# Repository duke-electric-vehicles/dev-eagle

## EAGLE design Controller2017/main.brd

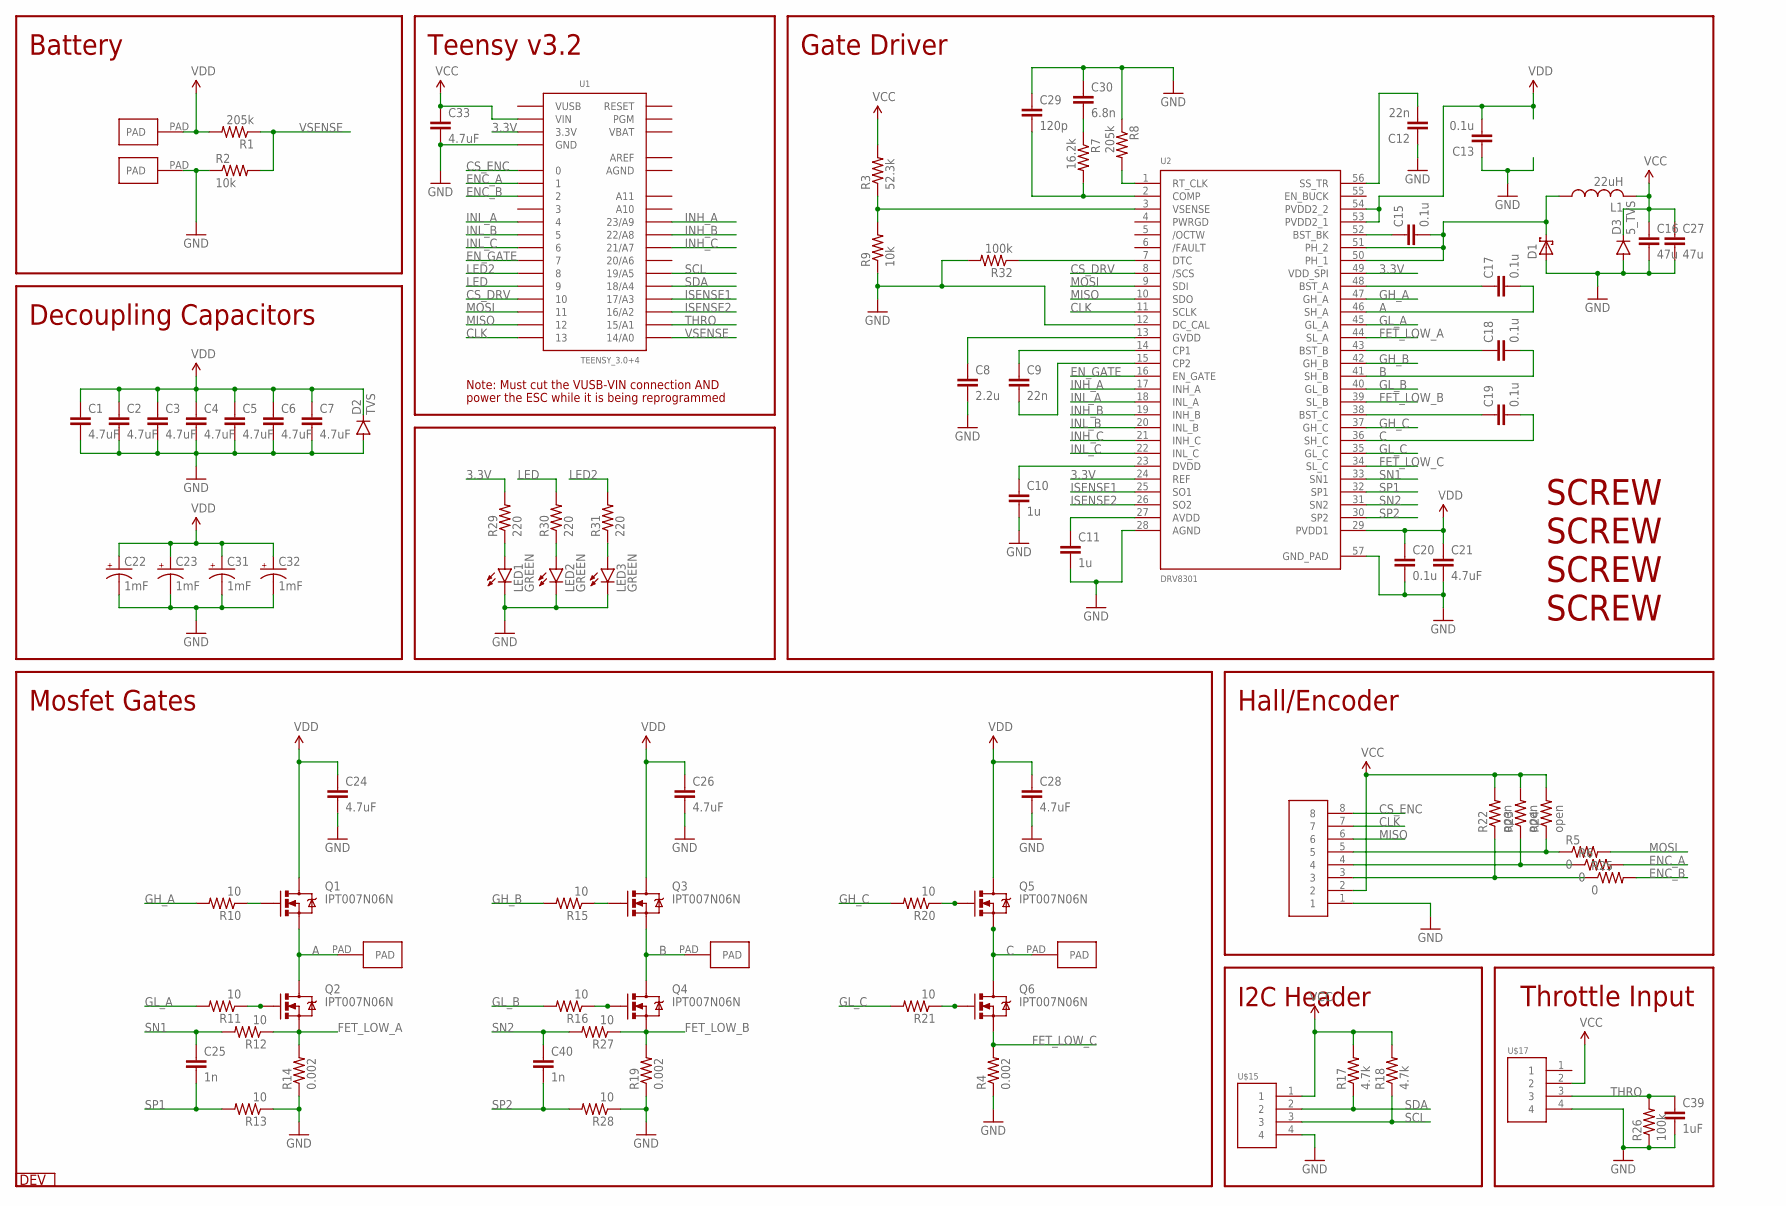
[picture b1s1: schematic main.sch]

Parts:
C1, C2, C3, C4, C5, C6, C7, C21, C24, C26, C28, C33: 4.7uF; 1206
C8: 2.2u; 0603-CAP
C9, C12: 22n; 0603-CAP
C10, C11: 1u; 0603-CAP
C13, C15, C17, C18, C19, C20: 0.1u; 0603-CAP
C16, C27: 47u; 0805
C22, C23, C31, C32: 1mF; CPOL-RADIAL-1000UF-25V
C25, C40: 1n; 0603-CAP
C29: 120p; 0603-CAP
C30: 6.8n; 0603-CAP
C39: 1uF; 0603-CAP
D1: SCHOTTKY_SMA; SMA
D2: TVS; SMC
D3: 5_TVS; SOT23-3
L1: 22uH; L5650M
LED1, LED2, LED3: GREEN; LED-1206
Q1, Q2, Q3, Q4, Q5, Q6: IPT007N06N; PG-HSOF-8-1
R1, R8: 205k; 0603-RES
R2, R9: 10k; 0603-RES
R3: 52.3k; 0603-RES
R4, R14, R19: 0.002; R2512
R5, R6, R25: 0; 0603-RES
R7: 16.2k; 0603-RES
R10, R11, R12, R13, R15, R16, R20, R21, R27, R28: 10; 0603-RES
R17, R18: 4.7k; 0603-RES
R22, R23, R24: open; 0603-RES
R26, R32: 100k; 0603-RES
R29, R30, R31: 220; 0603-RES
U1: TEENSY_3.0+4
U2: DRV8301
U$2: HEADER8; 8PINVALULOK
U$15, U$17: HEADER4VALULOK; 4PINVALULOK
U$16: DEV
U$19, U$20, U$21, U$22: SCREW; M3HOLE
U$23, U$24, U$25, U$26, U$27: PAD

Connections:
3.3V: R29.2, U1.3.3V, U1.3.3V1 (3.3V), U2.24 (REF), U2.49 (VDD_SPI)
A: C17.2, Q1.S, Q2.D, U2.46 (SH_A), U$23.PAD
AGND: U1.AGND
AREF: U1.AREF
B: C18.2, Q3.S, Q4.D, U2.41 (SH_B), U$24.PAD
C: C19.2, Q5.S, Q6.D, U2.36 (SH_C), U$25.PAD
CLK: U1.13, U2.11 (SCLK), U$2.7
CS_DRV: U1.10, U2.8 (/SCS)
CS_ENC: U1.0, U$2.8
ENC_A: R6.2, U1.1
ENC_B: R25.2, U1.2
EN_GATE: U1.7, U2.16 (EN_GATE)
FET_LOW_A: Q2.S, R12.1, R14.2, U2.44 (SL_A)
FET_LOW_B: Q4.S, R19.2, R27.1, U2.39 (SL_B)
FET_LOW_C: Q6.S, R4.2, U2.34 (SL_C)
GH_A: R10.2, U2.47 (GH_A)
GH_B: R15.2, U2.42 (GH_B)
GH_C: R20.2, U2.37 (GH_C)
GL_A: R11.2, U2.45 (GL_A)
GL_A': Q2.G, R11.1
GL_B: R16.2, U2.40 (GL_B)
GL_B': Q4.G, R16.1
GL_C: R21.2, U2.35 (GL_C)
GL_C': Q6.G, R21.1
GND: C1.2, C2.2, C3.2, C4.2, C5.2, C6.2, C7.2, C8.2, C10.2, C11.2, C12.1, C13.1, C16.2, C20.2, C21.2, C22.-, C23.-, C24.2, C26.2, C27.2, C28.2, C29.1, C30.1, C31.-, C32.-, C33.2, C39.2, D1.A, D2.A, D3.1 (A), LED1.C, LED2.C, LED3.C, R2.1, R4.1, R8.1, R9.1, R13.1, R14.1, R19.1, R26.1, R28.1, R32.2, U1.GND, U1.GND1 (GND), U2.12 (DC_CAL), U2.28 (AGND), U2.57 (GND_PAD), U$2.1, U$15.4, U$17.4, U$27.PAD
INH_A: U1.23/A9, U2.17 (INH_A)
INH_B: U1.22/A8, U2.19 (INH_B)
INH_C: U1.21/A7, U2.21 (INH_C)
INL_A: U1.4, U2.18 (INL_A)
INL_B: U1.5, U2.20 (INL_B)
INL_C: U1.6, U2.22 (INL_C)
ISENSE1: U1.17/A3, U2.25 (SO1)
ISENSE2: U1.16/A2, U2.26 (SO2)
LED: R30.2, U1.9
LED2: R31.2, U1.8
MISO: U1.12, U2.10 (SDO), U$2.6
MOSI: R5.2, U1.11, U2.9 (SDI)
unnamed: Q3.G, R15.1
unnamed: R3.1, R9.2, U2.3 (VSENSE)
unnamed: C29.2, R7.2, U2.2 (COMP)
unnamed: C10.1, U2.23 (DVDD)
unnamed: Q5.G, R20.1
unnamed: C12.2, U2.56 (SS_TR)
unnamed: C30.2, R7.1
unnamed: C15.1, U2.52 (BST_BK)
unnamed: Q1.G, R10.1
unnamed: R8.2, U2.1 (RT_CLK)
unnamed: LED1.A, R29.1
unnamed: R32.1, U2.7 (DTC)
unnamed: R5.1, R24.1, U$2.5
unnamed: R6.1, R23.1, U$2.4
unnamed: R22.1, R25.1, U$2.3
unnamed: LED2.A, R30.1
unnamed: LED3.A, R31.1
unnamed: C19.1, U2.38 (BST_C)
unnamed: C9.1, U2.14 (CP1)
unnamed: C11.1, U2.27 (AVDD)
unnamed: C9.2, U2.15 (CP2)
unnamed: C8.1, U2.13 (GVDD)
unnamed: C18.1, U2.43 (BST_B)
unnamed: C17.1, U2.48 (BST_A)
unnamed: C15.2, D1.C, L1.1, U2.50 (PH_1), U2.51 (PH_2)
SCL: R18.1, U1.19/A5, U$15.3
SDA: R17.1, U1.18/A4, U$15.2
SN1: C25.1, R12.2, U2.33 (SN1)
SN2: C40.1, R27.2, U2.31 (SN2)
SP1: C25.2, R13.2, U2.32 (SP1)
SP2: C40.2, R28.2, U2.30 (SP2)
THRO: C39.1, R26.2, U1.15/A1, U$17.3
VBAT: U1.VBAT
VCC: C16.1, C27.1, C33.1, D3.3 (C), L1.2, R3.2, R17.2, R18.2, R22.2, R23.2, R24.2, U1.VIN, U$2.2, U$15.1, U$17.2
VDD: C1.1, C2.1, C3.1, C4.1, C5.1, C6.1, C7.1, C13.2, C20.1, C21.1, C22.+, C23.+, C24.1, C26.1, C28.1, C31.+, C32.+, D2.C, Q1.D, Q3.D, Q5.D, R1.2, U2.29 (PVDD1), U2.53 (PVDD2_1), U2.54 (PVDD2_2), U$26.PAD
VSENSE: R1.1, R2.2, U1.14/A0
VUSB: U1.VUSB

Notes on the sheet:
Teensy v3.2
Gate Driver
Mosfet Gates
Battery
Hall/Encoder
Decoupling Capacitors
Note: Must cut the VUSB-VIN connection AND
power the ESC while it is being reprogrammed
Throttle Input
I2C Header

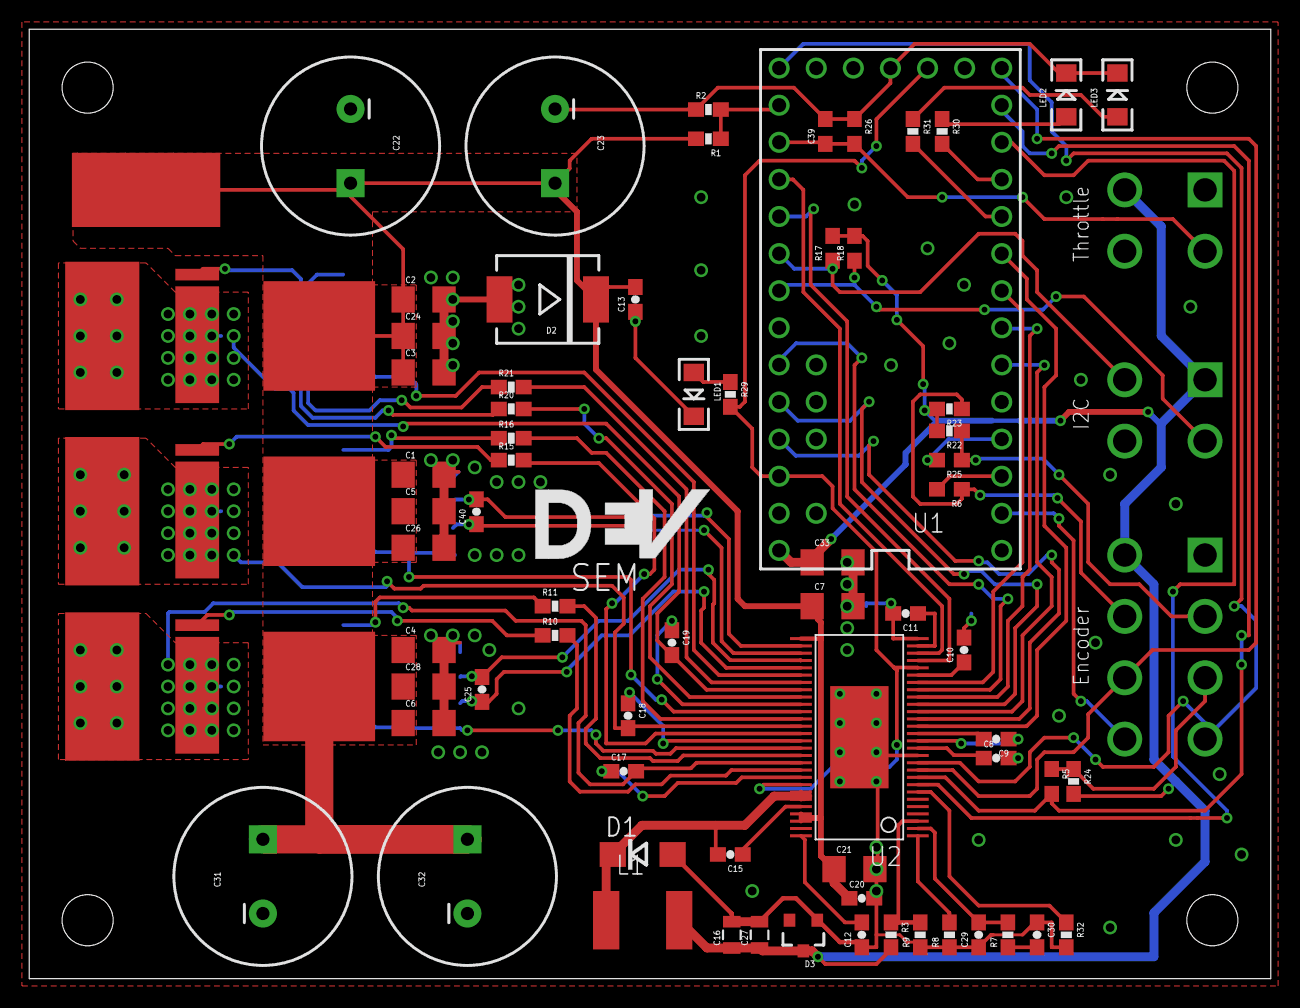
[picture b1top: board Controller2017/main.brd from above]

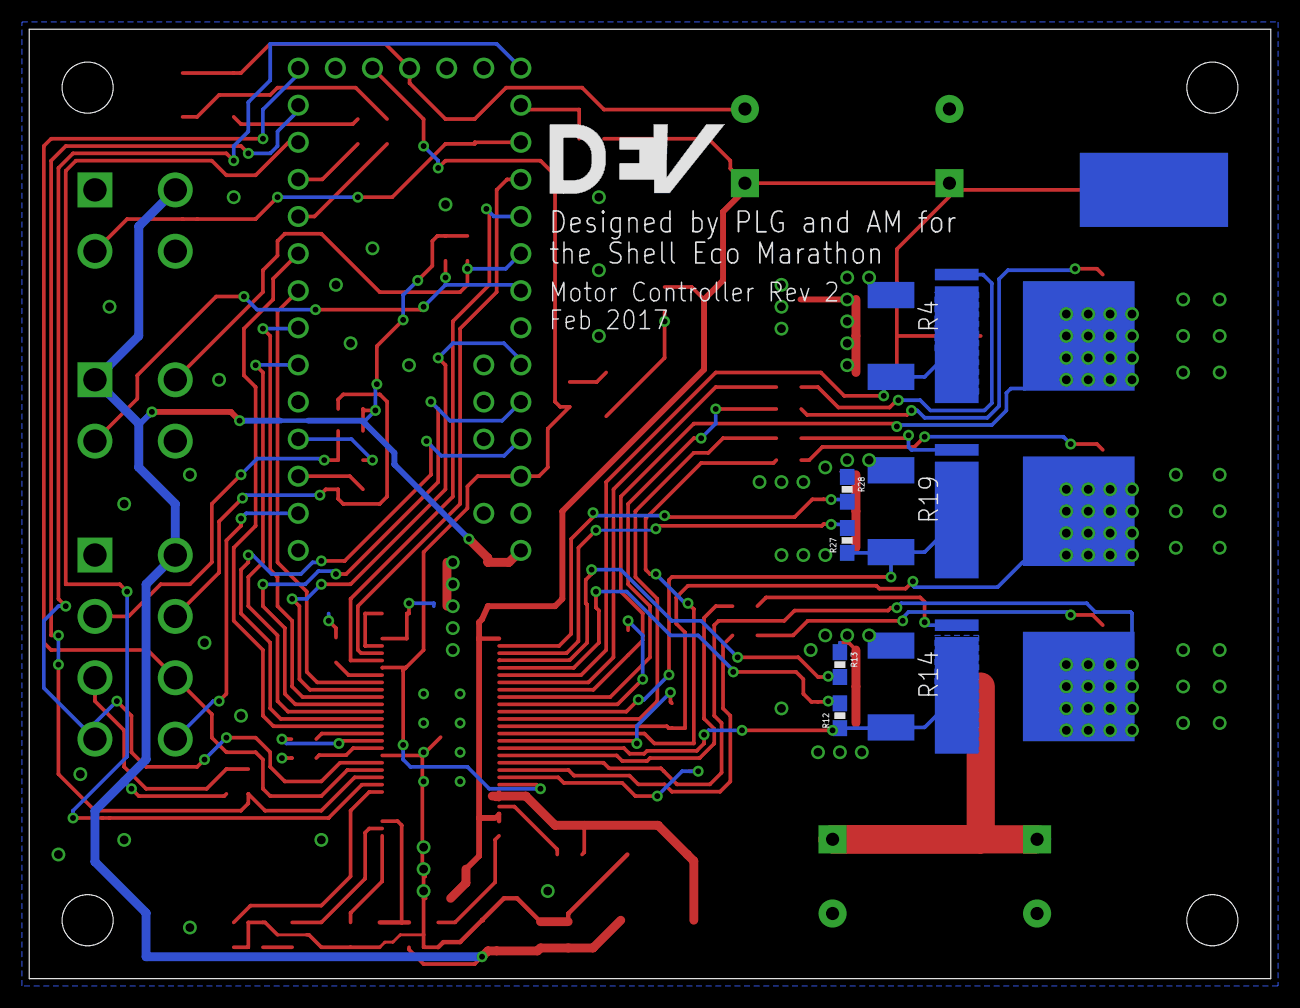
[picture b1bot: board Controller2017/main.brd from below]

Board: 2 copper layers, 85.0 x 65.0 mm, 95 parts (12 on the bottom side), 70 nets.

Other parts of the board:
U$28: DEV

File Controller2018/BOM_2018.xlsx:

Description | Digikey Part # | Value | Components | Price | Qty | Total |  | Grand total | 70.48
Teensy 3.2 | 1568-1231-ND |  | U1 | 22.5 | 1 | 22.5 | yes
DRV8301 | 296-29433-1-ND |  | U2 | 6.14 | 1 | 6.14 | yes
NFET | NVMFS5C404NLAFT1GOSCT-ND |  | Q1 Q2 Q3 Q4 Q5 Q6 | 3.47 | 6 | 20.82 | yes
TVS | 497-6522-1-ND | 48V | D2 | 0.53 | 1 | 0.53 | yes
TVS | GSOT05-E3-08CT-ND | 5v | D3 | 0.38 | 1 | 0.38 | yes
Quad Op-apm | 296-11968-1-ND |  |  | 2.0099999999999998 | 1 | 2.0099999999999998
PFET | 785-1001-1-ND |  |  | 0.48 | 1 | 0.48
 |  |  |  |  |  | 0
LED 1206 | 160-1456-1-ND | Green | LED1 LED2 LED3 | 0.34 | 3 | 1.02 | yes
Ceramic cap 50V 0603 | 490-1429-1-ND | 120pF | C29 | 0.01 | 1 | 0.01
Ceramic cap 50V 0603 | 399-1089-1-ND | 6.8nF | C30 | 0.01 | 1 | 0.01
Resistor 0603 | 311-16.2KHRCT-ND | 16.2k | R7 | 0.01 | 1 | 0.01
Resistor 0603 | 311-52.3KHRCT-ND | 52.3k | R3 | 0.01 | 1 | 0.01 | yes
Inductor | 587-2952-1-ND | 22uH | L1 | 0.43 | 1 | 0.43 | yes
Ceramic cap 6.3V 0805 | 311-1897-1-ND | 47uF | C16 C27 | 0.46 | 2 | 0.92
Schottkey diode | 641-1701-1-ND | 200V 3A | D1 | 0.43 | 1 | 0.43 | yes
Ceramic cap 16V 0603 | 490-3296-1-ND | 2.2uF | C8 | 0.1 | 1 | 0.1
Ceramic cap 50V 0603 | 490-1500-6-ND | 22nF | C9 C12 | 0.01 | 2 | 0.02 | yes
Ceramic cap 50V 0603 | 490-1519-6-ND | 0.1uF | C13 C15 C17 C18 C19 C20 C22 C23 | 0.01 | 8 | 0.08 | yes
Ceramic cap 25V 0805 | 490-3335-6-ND | 4.7uF | C14 C21 C35 | 0.1 | 3 | 0.30000000000000004
Ceramic cap 25V 0603 | 490-6339-6-ND | 10nF | C36 C37 C38 | 0.01 | 3 | 0.03
Resistor 0603 | 311-1.00KHRCT-ND | 1k | R5 R6 R25 | 0.01 | 3 | 0.03 | yes
Ceramic cap 50V 0603 | 587-3247-1-ND | 1uF | C10 C11 C39 | 0.12 | 3 | 0.36 | yes
Resistor 0603 | 311-4.70KHRCT-ND | 4.7k | R17 R18 | 0.01 | 2 | 0.02
Ceramic cap 50V 0603 | 478-1215-1-ND | 1nF | C25 | 0.01 | 1 | 0.01 | yes
Resistor 2512 | CSNL2512FT2L00DKR-ND | 2m | R4 R14 R19 | 0.53 | 3 | 1.59 | yes
Resistor 0603 | 311-10.0HRCT-ND | 10 | R10 R11 R12 R13 R15 R16 R20 R21 | 0.01 | 8 | 0.08 | yes
Resistor 0603 | 311-10.0KHRCT-ND | 10k | R2 R4 R9 R22 R23 R24 | 0.01 | 6 | 0.06 | yes
Resistor 0603 | 311-205KHRCT-ND | 205k | R1 R8 R26 | 0.01 | 3 | 0.03 | yes
Ceramic cap 50V 1206 | 587-2994-1-ND | 4.7uF | C1 C2 C3 C4 C5 C6 C7 C24 C26 C28 C33 | 0.15 | 11 | 1.65 | yes
Aluminum cap | 565-4618-ND | 1000uF | C22 C23 C31 C32 | 2.14 | 4 | 8.56 | yes
Resistor 0603 | 311-220HRCT-ND | 220 | R29 R30 R31 | 0.01 | 3 | 0.03
 |  |  |  |  |  | 0
VAL-U-LOK header | A30605-ND | 8 pin |  | 0.71 | 1 | 0.71 | yes
VAL-U-LOK header | A30603-ND | 4 pin |  | 0.56000000000000005 | 2 | 1.1200000000000001 | yes
 |  |  |  |  |  | 0
 |  |  |  |  |  | 0
 |  |  |  |  |  | 0
 |  |  |  |  |  | 0
 |  |  |  |  |  | 0
 |  |  |  |  |  | 0
 |  |  |  |  |  | 0
 |  |  |  |  |  | 0
 |  |  |  |  |  | 0
 |  |  |  |  |  | 0
 |  |  |  |  |  | 0
 |  |  |  |  |  | 0
 |  |  |  |  |  | 0
 |  |  |  |  |  | 0
 |  |  |  |  |  | 0
 |  |  |  |  |  | 0

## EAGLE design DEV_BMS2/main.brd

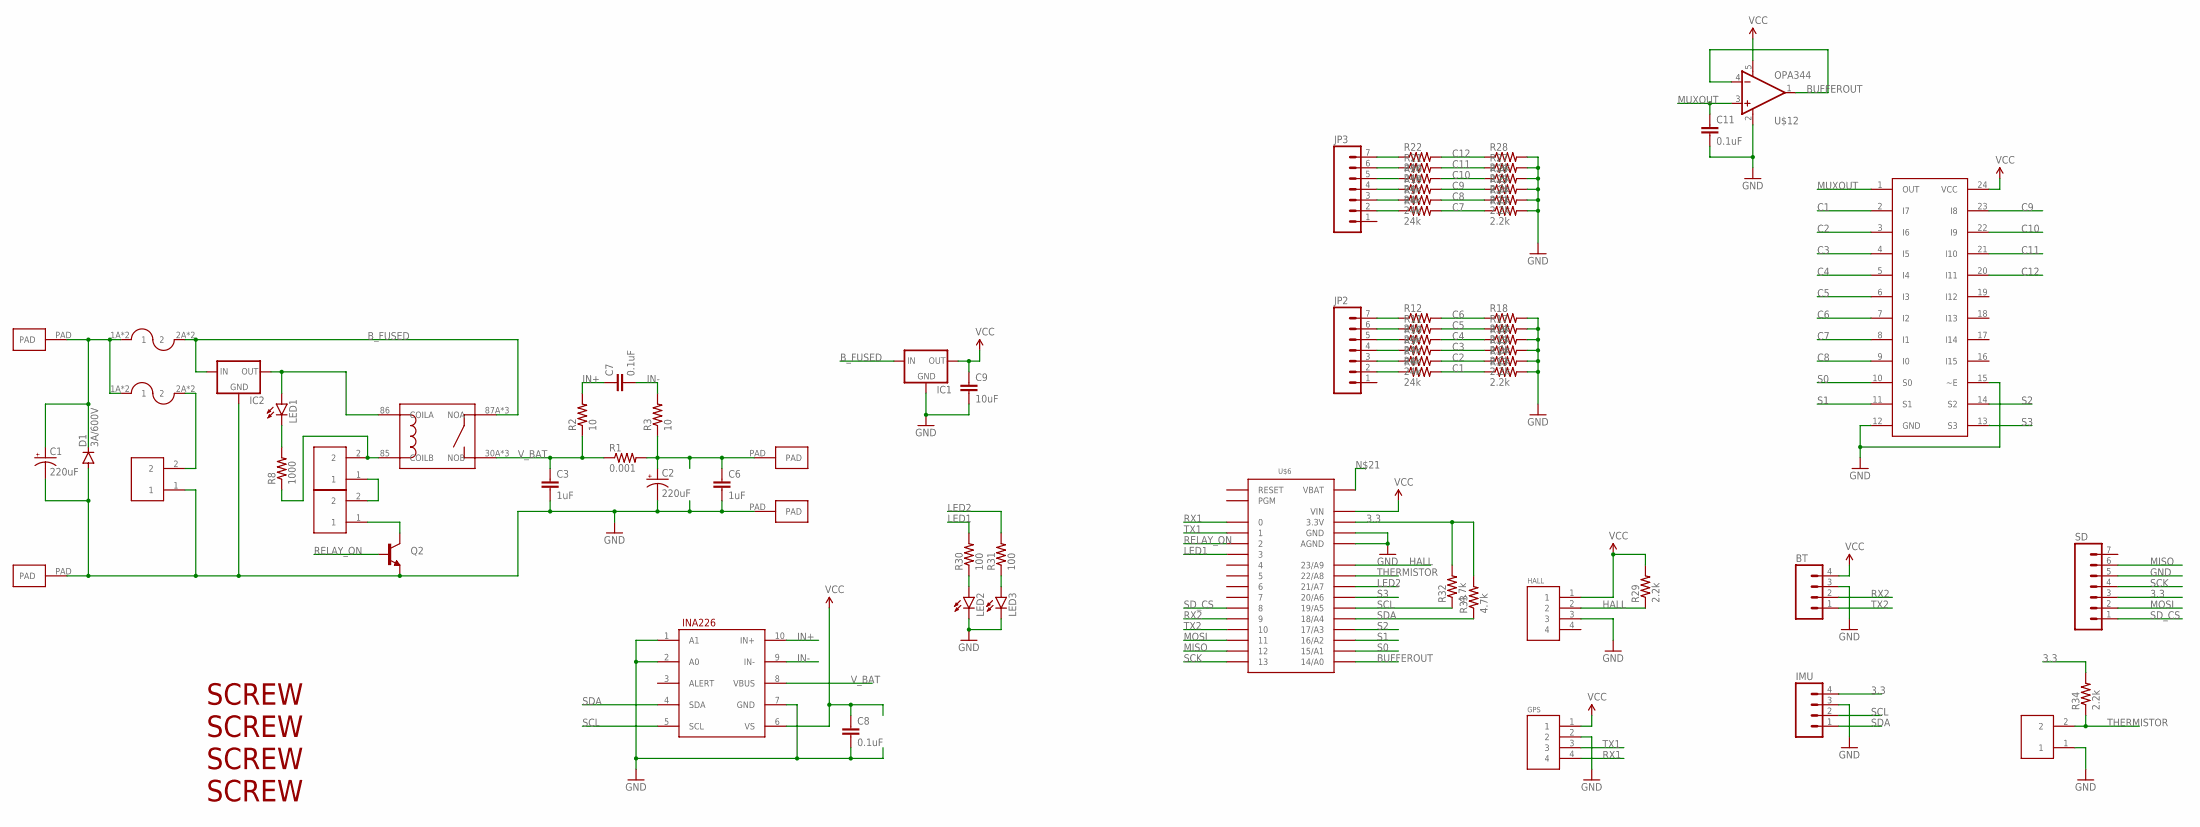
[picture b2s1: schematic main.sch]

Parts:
BT: M04PTH; 1X04
C1, C2: 220uF; CPOL-RADIAL-1000UF-25V
C3, C6: 1uF; 1206
C7, C8, C11: 0.1uF; 0603-CAP
C9: 10uF; 0805
D1: 3A/600V; SMC
GPS: GPS; 4PINVALULOK
HALL: HEADER4VALULOK; 4PINVALULOK
IC1, IC2: V_REG_78XXSINK; TO220-IGO
IMU: M04PTH; 1X04
JP2, JP3: M07; 1X07
LED1, LED2, LED3: LED1206; LED-1206
Q2: TRANSISTOR_NPNSMD2; SOT223
R1: 0.001; R2512
R2, R3: 10; 0603-RES
R4, R5, R6, R7, R9, R10, R11, R12, R19, R20, R21, R22: 24k; 0603-RES
R8: 1000; 0603-RES
R13, R14, R15, R16, R17, R18, R23, R24, R25, R26, R27, R28, R29, R34: 2.2k; 0603-RES
R30, R31: 100; 0603-RES
R32, R33: 4.7k; 0603-RES
SD: M07; 1X07
U$1: INA226; PSOP-10
U$2, U$3, U$4, U$5: PAD
U$6: TEENSY_3.0_BASIC
U$7: RELAY; PANASONIC_HP_RELAY
U$8, U$18: FUSE; AUTO_FUSE
U$9, U$10, U$17, U$19: HEADER2; 2PINVALULOK
U$11: CD74HC4067; SO-24DW
U$12: OPA344; SOT23-5
U$13, U$14, U$15, U$16: SCREW; M3HOLE

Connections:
3.3: IMU.4, R32.2, R33.2, R34.2, SD.3, U$6.3.3V, U$6.3.3V1 (3.3V)
BUFFEROUT: U$6.14/A0, U$12.1 (OUT), U$12.4 (-IN)
B_FUSED: IC1.IN, IC2.IN, U$7.87A (NOA), U$7.87B (NOA), U$7.87C (NOA), U$8.2A (2), U$8.2B (2)
B_OUT: C2.+, C6.1, R1.2, R3.1, U$4.PAD
B_RAW: C1.+, D1.C, U$2.PAD, U$8.1A (1), U$8.1B (1), U$18.1A (1), U$18.1B (1)
C1: R6.2, R13.1, U$11.2 (I7)
C2: R7.2, R14.1, U$11.3 (I6)
C3: R9.2, R15.1, U$11.4 (I5)
C4: R10.2, R16.1, U$11.5 (I4)
C5: R11.2, R17.1, U$11.6 (I3)
C6: R12.2, R18.1, U$11.7 (I2)
C7: R4.2, R23.1, U$11.8 (I1)
C8: R5.2, R24.1, U$11.9 (I0)
C9: R19.2, R25.1, U$11.23 (I8)
C10: R20.2, R26.1, U$11.22 (I9)
C11: R21.2, R27.1, U$11.21 (I10)
C12: R22.2, R28.1, U$11.20 (I11)
GND: BT.3, C1.-, C2.-, C3.2, C6.2, C8.2, C9.2, C11.2, D1.A, GPS.2, HALL.3, IC1.GND, IC2.GND, IMU.3, LED2.C, LED3.C, Q2.3 (E), R13.2, R14.2, R15.2, R16.2, R17.2, R18.2, R23.2, R24.2, R25.2, R26.2, R27.2, R28.2, SD.5, U$1.1 (A1), U$1.2 (A0), U$1.7 (GND), U$3.PAD, U$5.PAD, U$6.AGND, U$6.GND, U$6.GND1 (GND), U$11.12 (GND), U$11.15 (~E), U$12.2 (V-), U$17.1, U$19.1
HALL: HALL.2, R29.1, U$6.23/A9
IN+: C7.1, R2.2, U$1.10 (IN+)
IN-: C7.2, R3.2, U$1.9 (IN-)
LED1: R30.2, U$6.3
LED2: R31.2, U$6.21/A7
MISO: SD.6, U$6.12
MOSI: SD.2, U$6.11
MUXOUT: C11.1, U$11.1 (OUT), U$12.3 (+IN)
unnamed: JP2.7, R12.1
unnamed: LED2.A, R30.1
unnamed: JP2.6, R11.1
unnamed: JP2.5, R10.1
unnamed: U$18.2A (2), U$18.2B (2), U$19.2
unnamed: JP2.4, R9.1
unnamed: IC2.OUT, LED1.A, U$7.86 (COILA)
unnamed: JP2.3, R7.1
unnamed: LED1.C, R8.2
unnamed: R8.1, U$7.85 (COILB), U$9.2
unnamed: JP2.2, R6.1
unnamed: U$9.1, U$10.2
unnamed: Q2.2 (C), U$10.1
unnamed: JP3.7, R22.1
unnamed: JP3.6, R21.1
unnamed: JP3.5, R20.1
unnamed: JP3.4, R19.1
unnamed: JP3.3, R5.1
unnamed: JP3.2, R4.1
unnamed: LED3.A, R31.1
RELAY_ON: Q2.1 (B), U$6.2
RX1: GPS.4, U$6.0
RX2: BT.2, U$6.9
S0: U$6.15/A1, U$11.10 (S0)
S1: U$6.16/A2, U$11.11 (S1)
S2: U$6.17/A3, U$11.14 (S2)
S3: U$6.20/A6, U$11.13 (S3)
SCK: SD.4, U$6.13
SCL: IMU.2, R32.1, U$1.5 (SCL), U$6.19/A5
SDA: IMU.1, R33.1, U$1.4 (SDA), U$6.18/A4
SD_CS: SD.1, U$6.8
THERMISTOR: R34.1, U$6.22/A8, U$17.2
TX1: GPS.3, U$6.1
TX2: BT.1, U$6.10
VCC: BT.4, C8.1, C9.1, GPS.1, HALL.1, IC1.OUT, R29.2, U$1.6 (VS), U$6.VIN, U$11.24 (VCC), U$12.5 (V+)
V_BAT: C3.1, R1.1, R2.1, U$1.8 (VBUS), U$7.30A (NOB), U$7.30B (NOB), U$7.30C (NOB)

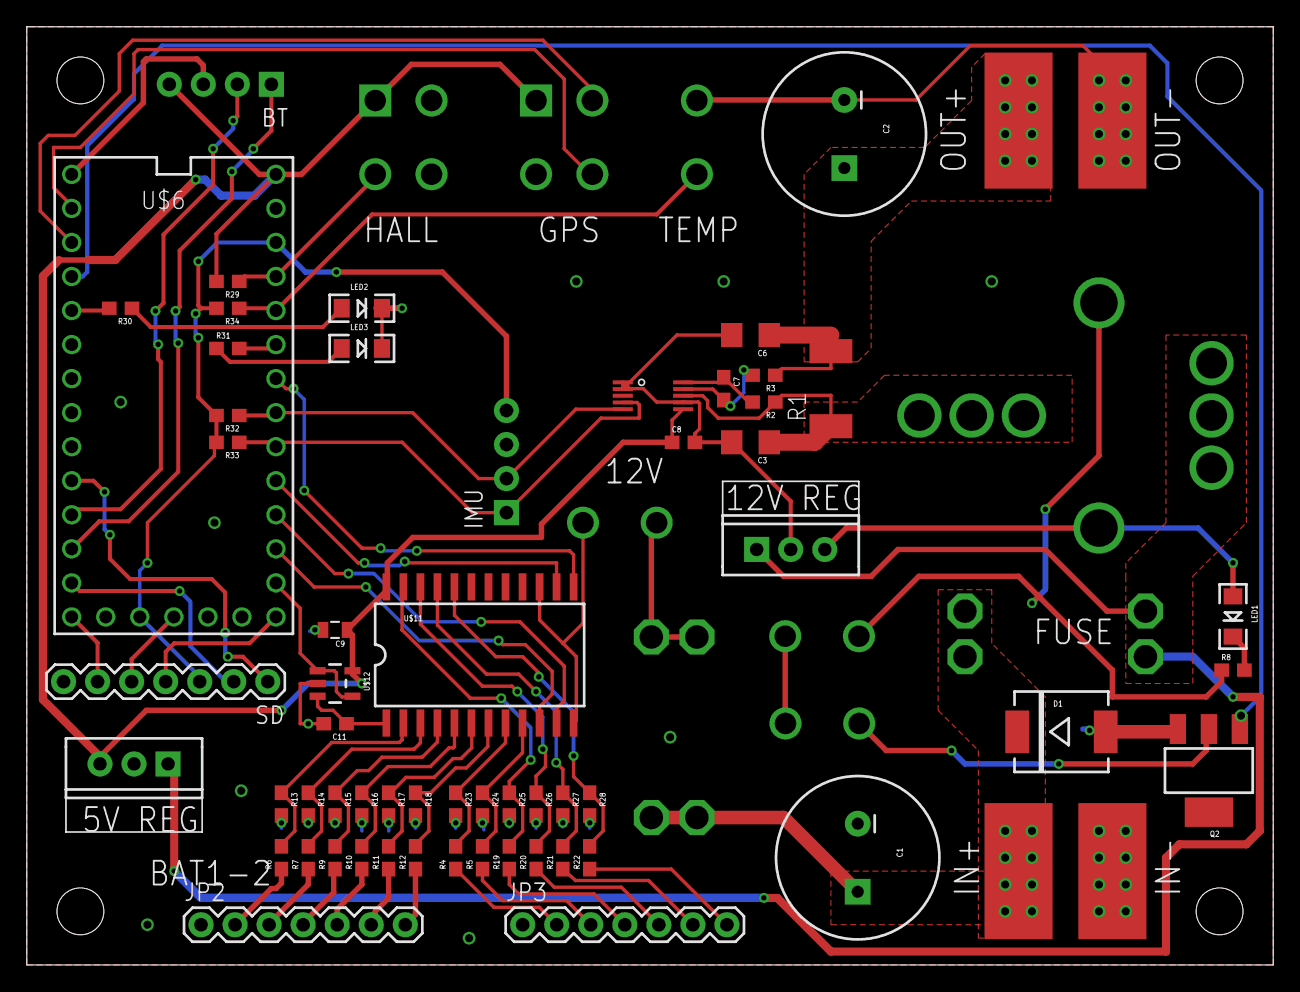
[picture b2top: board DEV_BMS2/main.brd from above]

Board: 2 copper layers, 93.0 x 70.0 mm, 75 parts (0 on the bottom side), 62 nets.

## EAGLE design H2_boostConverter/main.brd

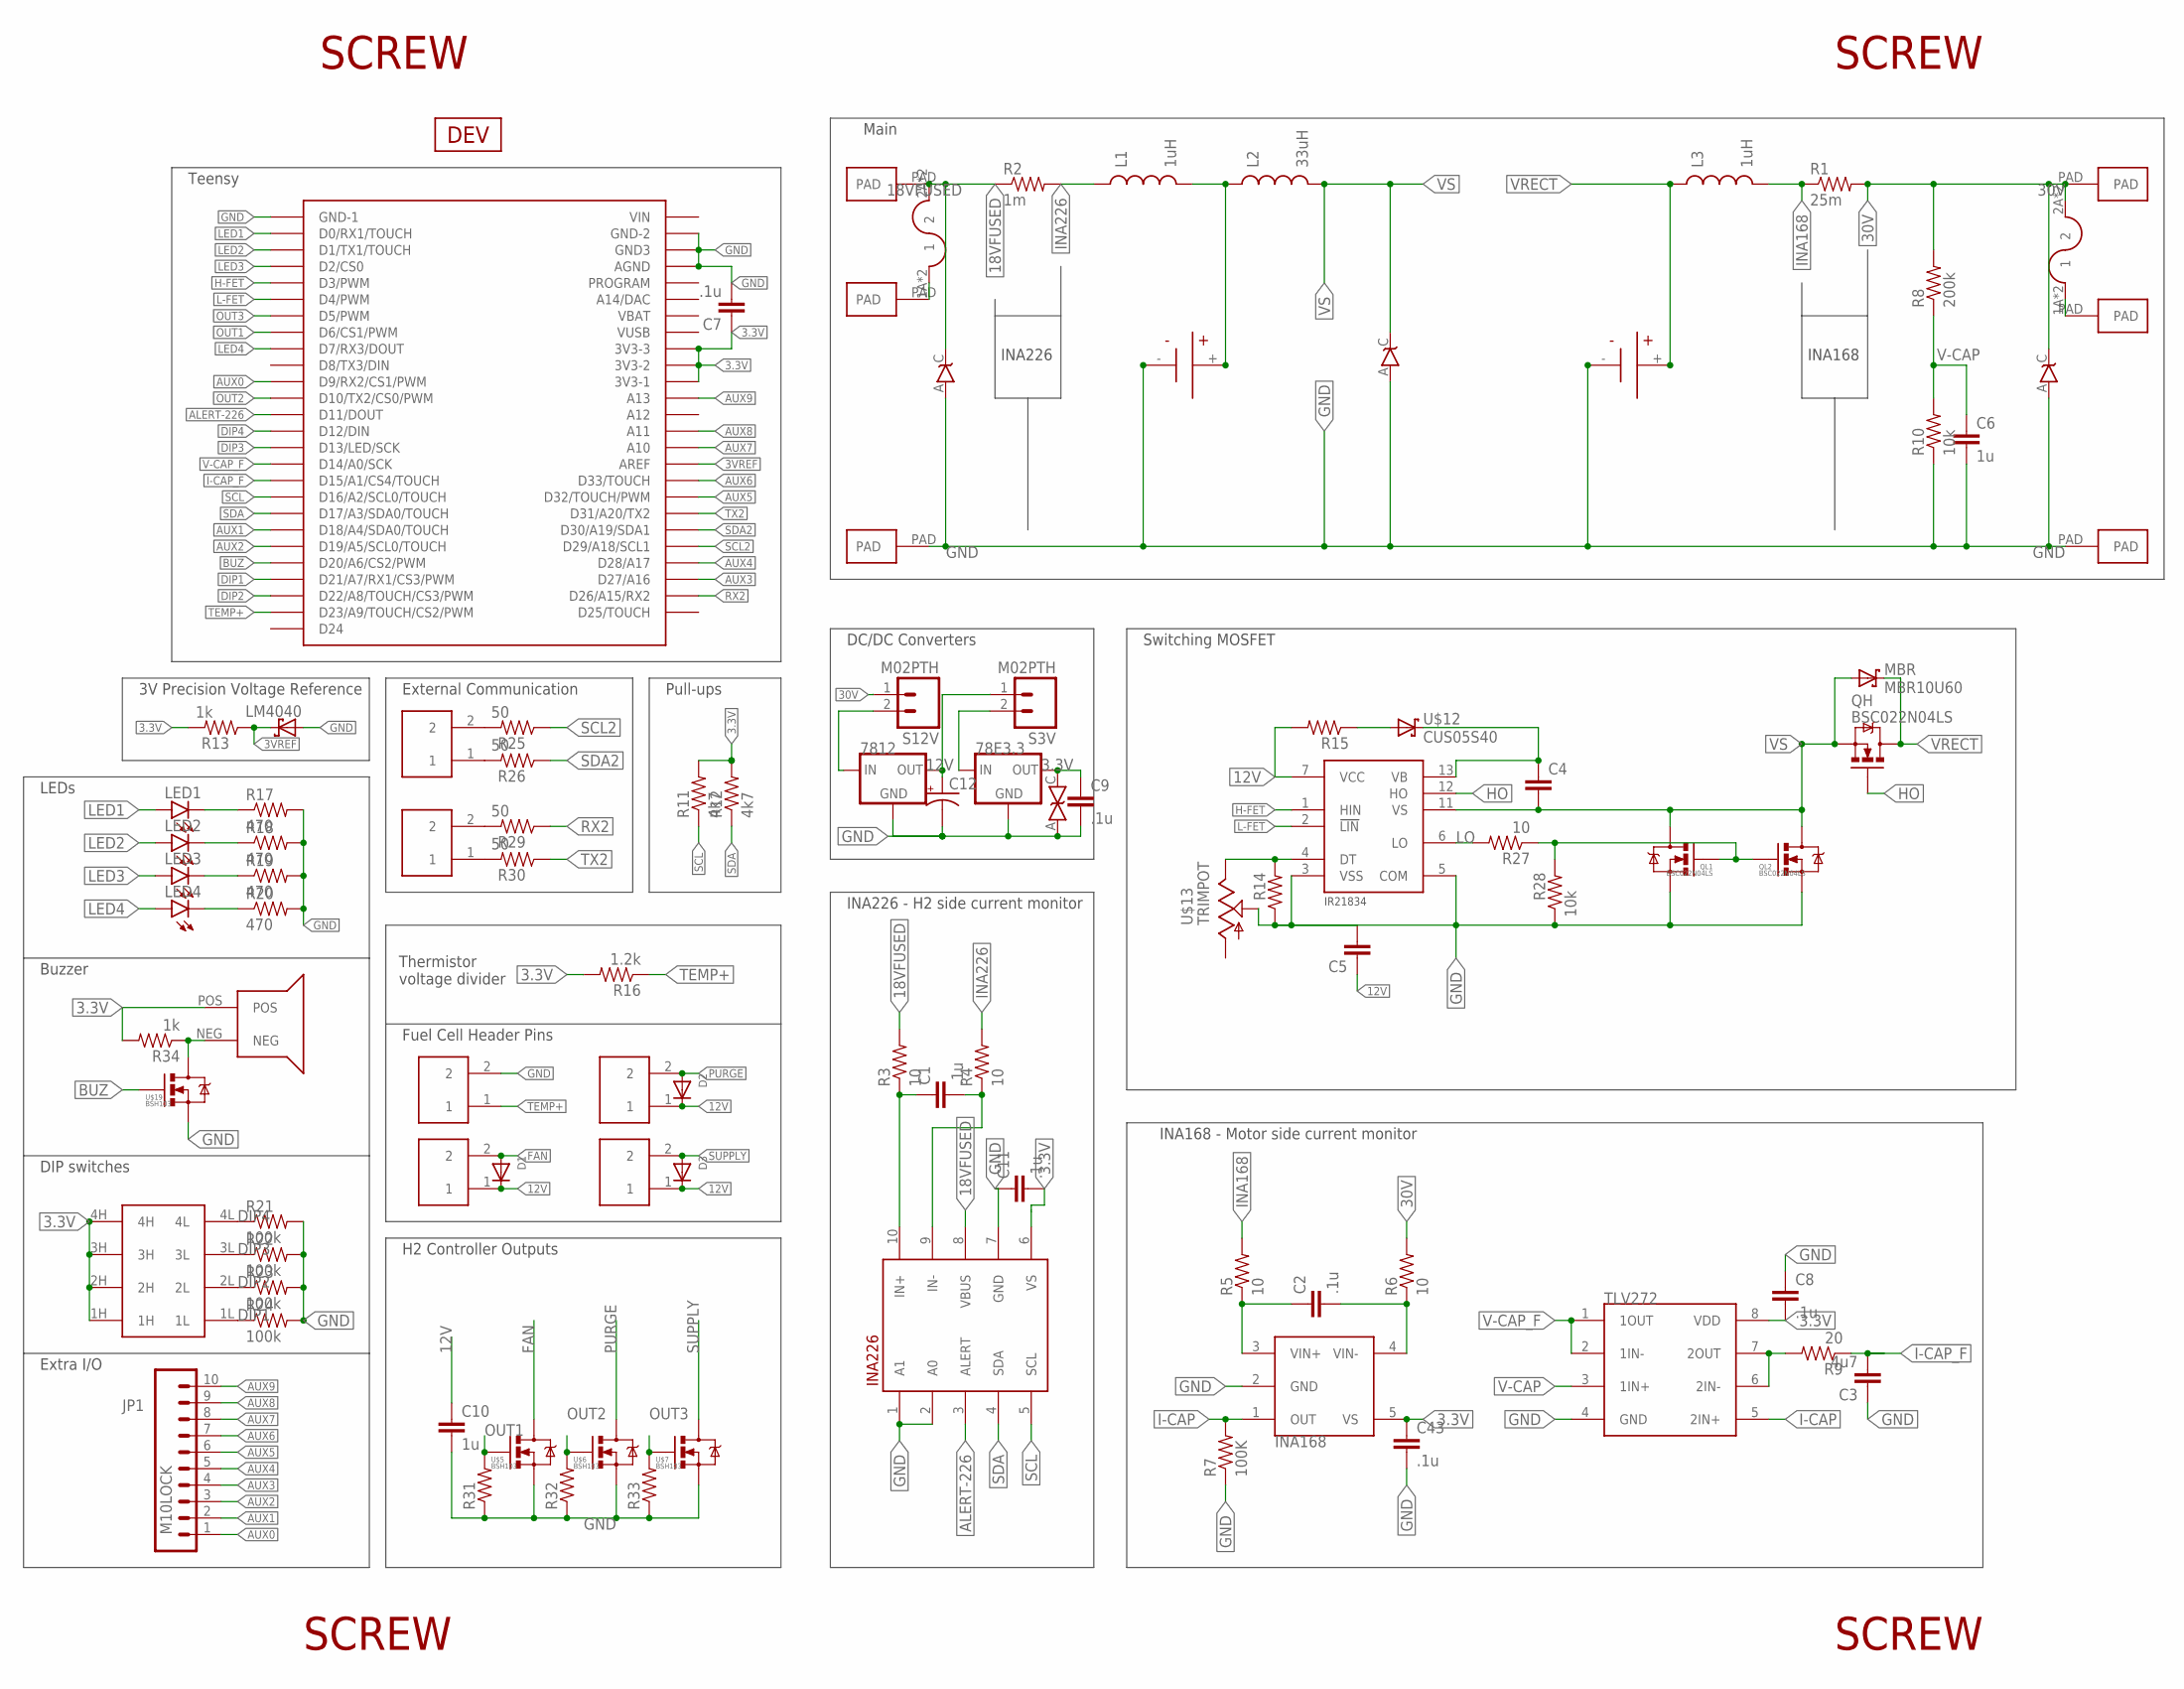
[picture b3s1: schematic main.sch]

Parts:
78E3.3: V_REG_78XXR-78E; V78W
7812: V_REG_78XX; V78W_BACKWARDS
C1, C2, C7, C8, C9, C11, C43: .1u; 0603-CAP
C1-1, C2-1: 2400u; CAP-RADIAL
C3: 4u7; 0603-CAP
C4, C5: CAP0603-CAP; 0603-CAP
C6, C10: 1u; 0603-CAP
C12: 10UF-25V-20%(PTH); CPOL-RADIAL-10UF-25V
D1, D2, D3: DIODESOT23_REFLOW; SOT23-R
FAN: HEADER2; 2PINVALULOK
I2C: HEADER2; 2PINVALULOK
INFUSE: FUSE; AUTO_FUSE
JP1: M10LOCK; 1X10_LOCK
L1, L3: 1uH; SER20XX
L2: 33uH; D1787
LED1, LED2, LED3, LED4: LED0603; LED-0603
MBR: MBR10U60; TO-277
OUTFUSE: FUSE; AUTO_FUSE
PURGEVALVE: HEADER2; 2PINVALULOK
QH: BSC022N04LS; PG-TDSON-8
QL1, QL2: BSC022N04LS; PG-TDSON-8
R1: 25m; R2512
R2: 1m; R2512
R3, R4, R5, R6: 10; 0603-RES
R7: 100K; 0603-RES
R8: 200k; 0603-RES
R9: 20; 0603-RES
R10, R28: 10k; 0603-RES
R11, R12: 4k7; 0603-RES
R13, R34: 1k; 0603-RES
R14, R15, R31, R32, R33: RESISTOR0603-RES; 0603-RES
R16: 1.2k; 0603-RES
R17, R18, R19, R20: 470; 0603-RES
R21, R22, R23, R24: 100k; 0603-RES
R25, R26, R29, R30: 50; 0603-RES
R27: 10; 0402-RES
S3V, S12V: M02PTH; 1X02
SERIAL2: HEADER2; 2PINVALULOK
SUPPLYVALVE: HEADER2; 2PINVALULOK
THERMISTOR: HEADER2; 2PINVALULOK
TVS1, TVS2, TVS3: TVS_UNIDO-214AB; DO-214AB
TVS4: 3.3V; SOD-523
U1: INA226; PSOP-10
U2: INA168INA168; SOT23-5
U3: TLV272; 8-VSSOP
U$1, U$2, U$3, U$10, U$16, U$24: PAD
U$5, U$6, U$7, U$19: BSH103; SOT23-3
U$8, U$11, U$17, U$29: SCREW; M3HOLE
U$9: IR21834; SO14
U$12: CUS05S40; SOD323_ST
U$13: TRIMPOT; 3MM_TRIMM
U$14: LM4040; SOT23-3
U$18: BUZZER12MM; BUZZER_12MM
U$20: DIP_SWITCH; DIPSWITCH4
U$21: DEV
U$26: TEENSY30-FULL

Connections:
3.3V: 78E3.3.OUT, C7.1, C8.2, C9.1, C11.2, C43.1, R11.2, R12.2, R13.2, R16.2, R34.2, TVS4.C (2), U1.6 (VS), U2.5 (VS), U3.8 (VDD), U$18.POS, U$20.1H, U$20.2H, U$20.3H, U$20.4H, U$26.3V3 (3V3-1), U$26.3V3-1 (3V3-2), U$26.3V3-2 (3V3-3)
3VREF: R13.1, U$14.1 (C), U$26.AREF
12V: 7812.OUT, C5.1, C10.1, C12.1 (+), D1.3 (C), D2.3 (C), D3.3 (C), FAN.1, PURGEVALVE.1, R15.2, S3V.1, SUPPLYVALVE.1, U$9.7 (VCC)
18V: INFUSE.1A (1), INFUSE.1B (1), U$24.PAD
18VFUSED: INFUSE.2A (2), INFUSE.2B (2), R2.1, R3.2, TVS1.C, U1.8 (VBUS), U$3.PAD
30V: OUTFUSE.2A (2), OUTFUSE.2B (2), R1.2, R6.2, R8.2, S12V.1, TVS3.C, U$1.PAD
30VFUSED: OUTFUSE.1A (1), OUTFUSE.1B (1), U$16.PAD
ALERT-226: U1.3 (ALERT), U$26.D11/DOUT
AUX0: JP1.1, U$26.D9/RX2/CS1/PWM
AUX1: JP1.2, U$26.D18/A4/SDA/TOUCH (D18/A4/SDA0/TOUCH)
AUX2: JP1.3, U$26.D19/A5/SCL/TOUCH (D19/A5/SCL0/TOUCH)
AUX3: JP1.4, U$26.D27 (D27/A16)
AUX4: JP1.5, U$26.D28 (D28/A17)
AUX5: JP1.6, U$26.D32/TOUCH (D32/TOUCH/PWM)
AUX6: JP1.7, U$26.D33/TOUCH
AUX7: JP1.8, U$26.A10
AUX8: JP1.9, U$26.A11
AUX9: JP1.10, U$26.A13
BUZ: U$19.1 (G), U$26.D20/A6/CS2/PWM
DIP1: R24.1, U$20.1L, U$26.D21/A7/RX1/CS3/PWM
DIP2: R23.1, U$20.2L, U$26.D22/A8/TOUCH/CS3/PWM
DIP3: R22.1, U$20.3L, U$26.D13/LED/SCK
DIP4: R21.1, U$20.4L, U$26.D12/DIN
DT: R14.2, U$9.4 (DT), U$13.3 (E)
FAN: D1.1 (A), FAN.2, U$5.3 (D)
GND: 78E3.3.GND, 7812.GND, C1-1.- (V-), C2-1.- (V-), C3.1, C5.2, C6.2, C7.2, C8.1, C9.2, C10.2, C11.1, C12.2 (-), C43.2, QL1.1 (S), QL1.2 (S), QL1.3 (S), QL2.1 (S), QL2.2 (S), QL2.3 (S), R7.1, R10.1, R14.1, R17.2, R18.2, R19.2, R20.2, R21.2, R22.2, R23.2, R24.2, R28.1, R31.1, R32.1, R33.1, THERMISTOR.2, TVS1.A, TVS2.A, TVS3.A, TVS4.A (1), U1.1 (A1), U1.2 (A0), U1.7 (GND), U2.2 (GND), U3.4 (GND), U$2.PAD, U$5.2 (S), U$6.2 (S), U$7.2 (S), U$9.3 (VSS), U$9.5 (COM), U$10.PAD, U$13.2 (S), U$14.2 (A), U$19.2 (S), U$26.AGND, U$26.GND-1, U$26.GND-2, U$26.GND-3 (GND3)
H-FET: U$9.1 (HIN), U$26.D3/PWM
HO: QH.4 (G), U$9.12 (HO)
I-CAP: R7.2, U2.1 (OUT), U3.5 (2IN+)
I-CAP_F: C3.2, R9.1, U$26.D15/A1/CS4/TOUCH
INA168: L3.1 (0), R1.1, R5.2
INA226: L1.2 (1), R2.2, R4.2
L-FET: U$9.2 (LIN), U$26.D4/PWM
LED1: LED1.A, U$26.D0/RX1/TOUCH
LED2: LED2.A, U$26.D1/TX1/TOUCH
LED3: LED3.A, U$26.D2/CS0
LED4: LED4.A, U$26.D7/RX3/DOUT
LO: QL1.4 (G), QL2.4 (G), R27.1, R28.2
unnamed: C1.1, R3.1, U1.10 (IN+)
unnamed: C2.1, R5.1, U2.3 (VIN+)
unnamed: C1.2, R4.1, U1.9 (IN-)
unnamed: C2.2, R6.1, U2.4 (VIN-)
unnamed: R15.1, U$12.A
unnamed: C1-1.+ (V+), L1.1 (0), L2.P$2 (1)
unnamed: LED1.C, R17.1
unnamed: LED2.C, R18.1
unnamed: R9.2, U3.6 (2IN-), U3.7 (2OUT)
unnamed: LED3.C, R19.1
unnamed: LED4.C, R20.1
unnamed: I2C.2, R25.2
unnamed: I2C.1, R26.2
unnamed: R34.1, U$18.NEG, U$19.3 (D)
unnamed: R27.2, U$9.6 (LO)
unnamed: 78E3.3.IN, S3V.2
unnamed: 7812.IN, S12V.2
unnamed: R29.2, SERIAL2.2
unnamed: R30.2, SERIAL2.1
OUT1: R31.2, U$5.1 (G), U$26.D6/CS1/PWM
OUT2: R32.2, U$6.1 (G), U$26.D10/TX2/CS0/PWM
OUT3: R33.2, U$7.1 (G), U$26.D5/TX1/PWM (D5/PWM)
PURGE: D2.1 (A), PURGEVALVE.2, U$6.3 (D)
RX2: R29.1, U$26.D26/RX2 (D26/A15/RX2)
SCL: R11.1, U1.5 (SCL), U$26.D16/A2/SCL/TOUCH (D16/A2/SCL0/TOUCH)
SCL2: R25.1, U$26.D29 (D29/A18/SCL1)
SDA: R12.1, U1.4 (SDA), U$26.D17/A3/SDA/TOUCH (D17/A3/SDA0/TOUCH)
SDA2: R26.1, U$26.D30 (D30/A19/SDA1)
SUPPLY: D3.1 (A), SUPPLYVALVE.2, U$7.3 (D)
TEMP+: R16.1, THERMISTOR.1, U$26.D23/A9/TOUCH/CS2/PWM
TX2: R30.1, U$26.D31/TX2 (D31/A20/TX2)
V-CAP: C6.1, R8.1, R10.2, U3.3 (1IN+)
V-CAP_F: U3.1 (1OUT), U3.2 (1IN-), U$26.D14/A0/SCK
VB: C4.1, U$9.13 (VB), U$12.C
VRECT: C2-1.+ (V+), L3.2 (1), MBR.3 (C), QH.5 (D), QH.6 (D), QH.7 (D), QH.8 (D), QH.TH (D)
VS: C4.2, L2.P$1 (0), MBR.1 (A), MBR.2 (A), QH.1 (S), QH.2 (S), QH.3 (S), QL1.5 (D), QL1.6 (D), QL1.7 (D), QL1.8 (D), QL1.TH (D), QL2.5 (D), QL2.6 (D), QL2.7 (D), QL2.8 (D), QL2.TH (D), TVS2.C, U$9.11 (VS)

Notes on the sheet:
INA226
INA168
INA226 - H2 side current monitor
INA168 - Motor side current monitor
Main
Switching MOSFET
H2 Controller Outputs
DC/DC Converters
Teensy
Fuel Cell Header Pins
Thermistor voltage divider
Pull-ups
External Communication
3V Precision Voltage Reference
LEDs
Buzzer
DIP switches
Extra I/O

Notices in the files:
parts and their libraries:
SparkFun-Capacitors: Licensing: Creative Commons ShareAlike 4.0 International - https://creativecommons.org/licenses/by-sa/4.0
